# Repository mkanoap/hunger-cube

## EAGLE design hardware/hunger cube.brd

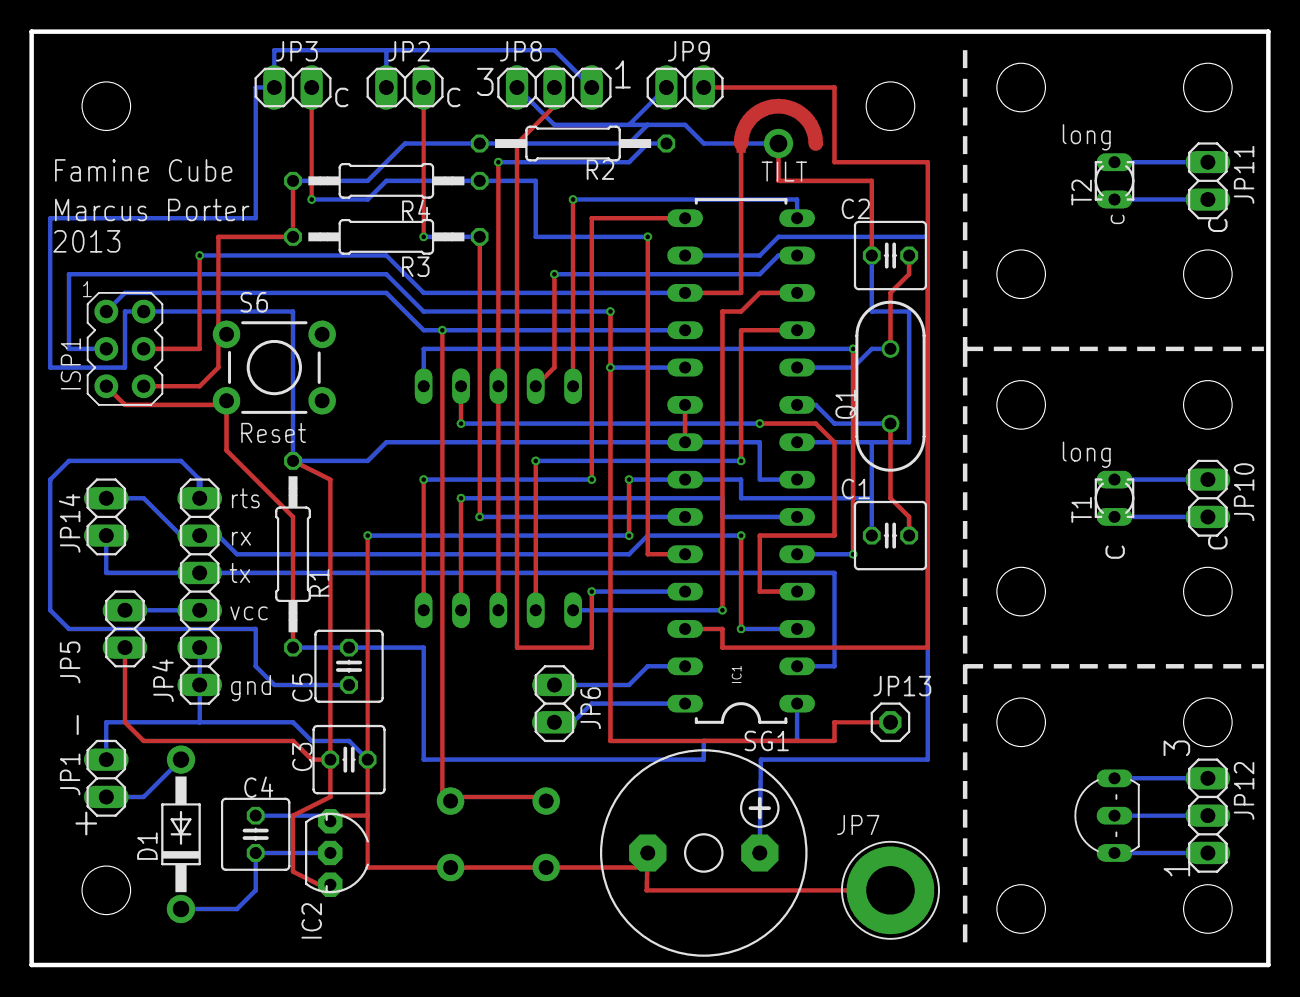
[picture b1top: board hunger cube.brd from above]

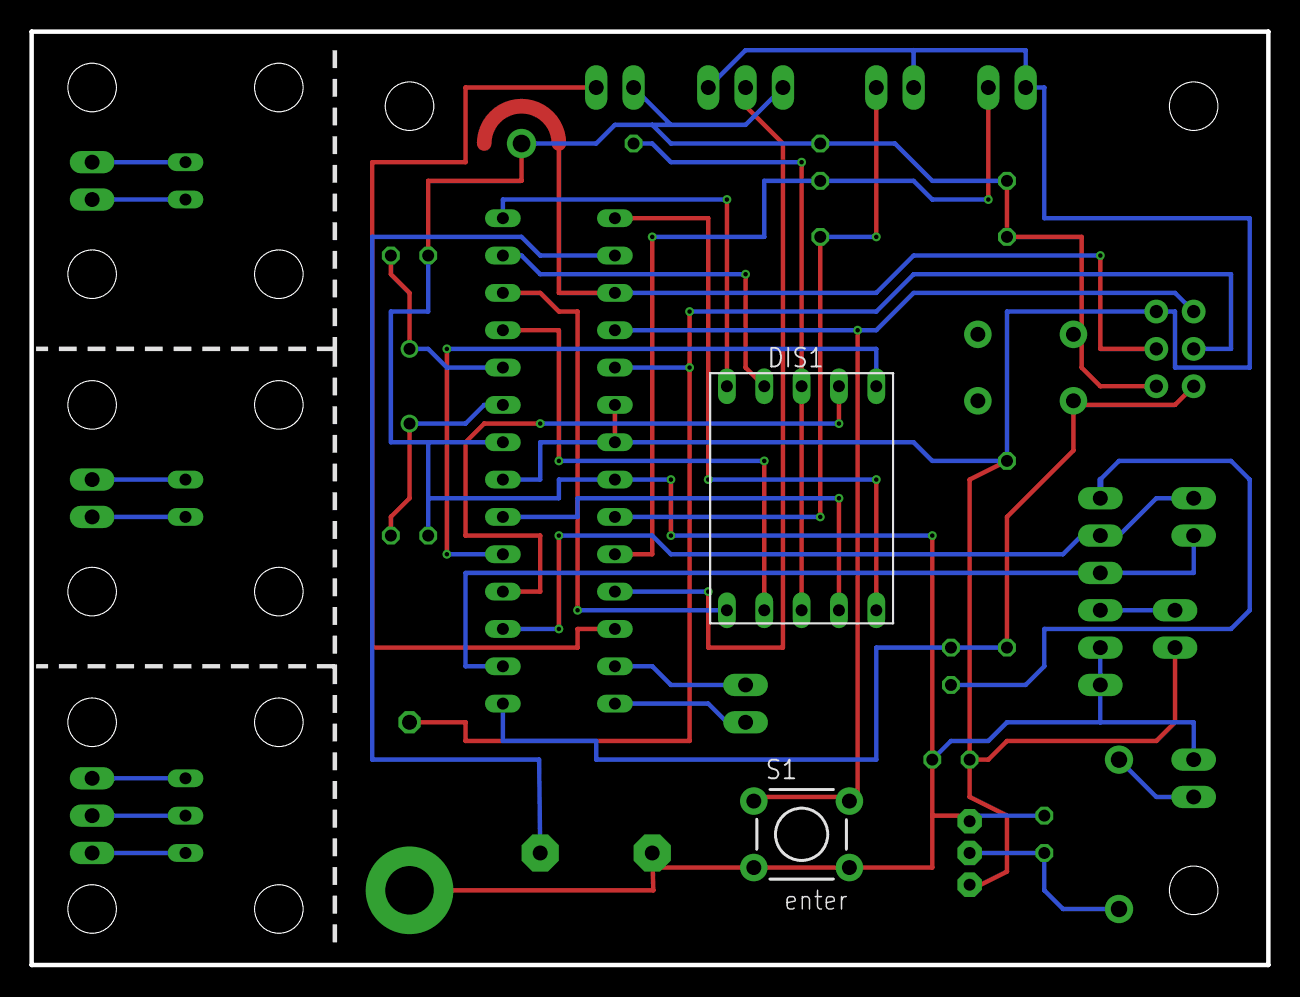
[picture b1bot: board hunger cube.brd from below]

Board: 2 copper layers, 84.1 x 63.5 mm, 39 parts (2 on the bottom side), 37 nets.

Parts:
C1, C2: 18pF; C025-050X050
C3, C4: 1uf; C025-050X050
C5: .1uf; C025-050X050
D1: DO41-10
DIS1: display; HDSP-M
IC1: AVR-MEGA8-PPTH; DIL28-3
IC2: LDO 5v; TO92-INLINE
ISP1: AVRISP-6; AVRISP
JP1: Battery; 1X02
JP2: Light1; 1X02
JP3: Light2; 1X02
JP4: FTDI; 1X06
JP5: Aux Pwr; 1X02
JP6: A5 A4; 1X02
JP7: Connected screw hole; SCREW-HOLE-PAD
JP8: TEMP; 1X03
JP9: Magnet; 1X02
JP10: RLight1; 1X02
JP11: Rlight2; 1X02
JP12: Rtemp; 1X03
JP13: R screw; 1X01
JP14: D0 D1; 1X02
Q1: 16Mhz; HC49US
R1, R3, R4: 10K; 0207/12
R2: 100; 0207/12
S1: enter; TACTILE-PTH
S6: reset; TACTILE-PTH
SG1: F/CM12P
ST1, ST2, ST3: STAND-OFF
T1, T2: light; BPX81
TEMPERATURE: Temperature; TO92-EBC
TILT: TILT-SENSOR; TILT

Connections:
+5V: C3.1, IC1.7, IC1.20, IC1.21, IC2.3, ISP1.2, JP2.1, JP3.1, JP5.1, JP8.3, R1.2
A0-LIGHT1: IC1.23, JP2.2, R3.1
A1-LIGHT2: IC1.24, JP3.2, R4.1
A2-TEMP: IC1.25, JP8.2
A3-MAGNET: IC1.26, JP9.2
A4: IC1.27, JP6.1
A5: IC1.28, JP6.2
D0-RDX: IC1.2, JP4.4, JP14.1
D1-TDX: IC1.3, JP4.5, JP14.2
D2-SEGA: DIS1.7, IC1.4
D3-SEBB: DIS1.6, IC1.5
D4-SEGC: DIS1.4, IC1.6
D5-SEGD: DIS1.2, IC1.11
D6-SEGE: DIS1.1, IC1.12
D7-SEGF: DIS1.9, IC1.13
D8-SEGG: DIS1.10, IC1.14
D9-DP: DIS1.5, IC1.15
D10-BUZZER: IC1.16, SG1.+
D11-MOSI-TILT: IC1.17, ISP1.4, TILT.SLEEVE
D12-MISO-ENTER: IC1.18, ISP1.1, S1.1, S1.2
D13-SCK-SCREW: IC1.19, ISP1.3, JP13.1
DSP-GND: DIS1.3, DIS1.8, R2.2
GND: C1.1, C2.1, C3.2, C4.2, IC1.8, IC1.22, IC2.1, ISP1.6, JP1.2, JP4.1, JP4.2, JP7.SCREW, JP8.1, JP9.1, R2.1, R3.2, R4.2, S1.3, S1.4, S6.1, SG1.-, TILT.CENTER
unnamed: C5.2, JP4.6
unnamed: D1.A, JP1.1
unnamed: C1.2, IC1.9, Q1.2
unnamed: C2.2, IC1.10, Q1.1
unnamed: JP4.3, JP5.2
unnamed: JP10.2, T1.E
unnamed: JP11.2, T2.E
unnamed: JP11.1, T2.C
unnamed: JP10.1, T1.C
unnamed: JP12.3, TEMPERATURE.E
unnamed: JP12.2, TEMPERATURE.B
unnamed: JP12.1, TEMPERATURE.C
RST: C5.1, IC1.1, ISP1.5, R1.1, S6.3
VCC: C4.1, D1.C, IC2.2

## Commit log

2013-03-04 Initial directory structure.
2013-03-05 implemented light, magnet and temperature sensors.
2013-03-14 added custom parts for tilt sensor and the secret screw. Laid out board for the first time.
2013-03-20 Added box svg to archive, measured dimentions of parts of board for box, and tweaked where some holes are.
2013-07-02 font changes
2015-05-05 Migrating wiki contents from Google Code
